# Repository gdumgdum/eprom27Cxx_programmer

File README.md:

# Programmer for EPROM 27 series (27C16-801/2KB-1MB) based on Arduino Micro

Programming is made possible by a dedicated hardware (made of a PCB, a few very common SMD components and an Arduino Micro), and a Qt software that can be compiled for Windows, Linux and MacOS.

Compatible Eprom List (not all chips were tested):

 * 27C16 (2KB)
 * 27C32 (4KB)
 * 27C64 (8KB)
 * 27C128 (16KB)
 * 27C256 (32KB)
 * 27C512 (64KB)
 * 27C1001 (128KB)
 * 27C2001 (256KB)
 * 27C4001 (512KB)
 * 27C801 (1MB)

Selected chip needs to be inserted in the ZIF socket at the lowest position possible (bottom aligned).

Before writing, activate the Voltage functionality, then adjust the potentiometer and compare the measured value with the one specified in the datasheet of the selected eprom. 

# Schematic

Based on the project https://github.com/walhi/arduino_eprom27_programmer, which was based on https://github.com/bouletmarc/BMBurner

PCB is now generated with [Kicad](https://www.kicad.org)

Gerber files generated by Kicad are located [here](https://github.com/gdumgdum/eprom27Cxx_programmer/blob/master/Kicad/Gerber/)

# Software

Software for Windows/Mac/Linux is written with Qt5.

Functions:

 * Read chip to memory buffer and check if chip is blank
 * Save memory buffer to file
 * Read memory buffer from file
 * Program chip with memory buffer
 * Read chip and compare to memory buffer 
 * Programming voltage control

# History

## PCB

* Switched to Arduino Micro model because the Nano version used in the previous version doesn't have enough inputs/outputs to handle all the programming modes.
* Pull-down resistors added to the lines where signal/power is sent through diodes.
* Programming voltage is now only generated from the +5V provided by the Arduino.
* A connector is available to connect to an external power-supply if the USB is not able to provide enough current (should not be necessary if connected to a USB-3 socket).

## Arduino Micro

* Added a reset routine because Micro is not reset when the COM port is opened, contrary to Nano.
* Added a decent synchronisation between Qt application and Arduino when programming the Eprom.
* Added a delay before reading/writting to allow voltages to stabilize.
* Added support for 27C1001, 27C2001, 27C4001 and 27C801.
* Increased communication speed with Qt application to 115200 bauds.

## Qt application

* Detached the buffer display in an independant window.
* Allow main window resizing.
* Fixed the progress bar display on MacOS.
* Added support for 27C1001, 27C2001, 27C4001 and 27C801.
* Added a decent synchronisation between Qt application and Arduino when programming the Eprom.
* Increased communication speed with Arduino to 115200 bauds.

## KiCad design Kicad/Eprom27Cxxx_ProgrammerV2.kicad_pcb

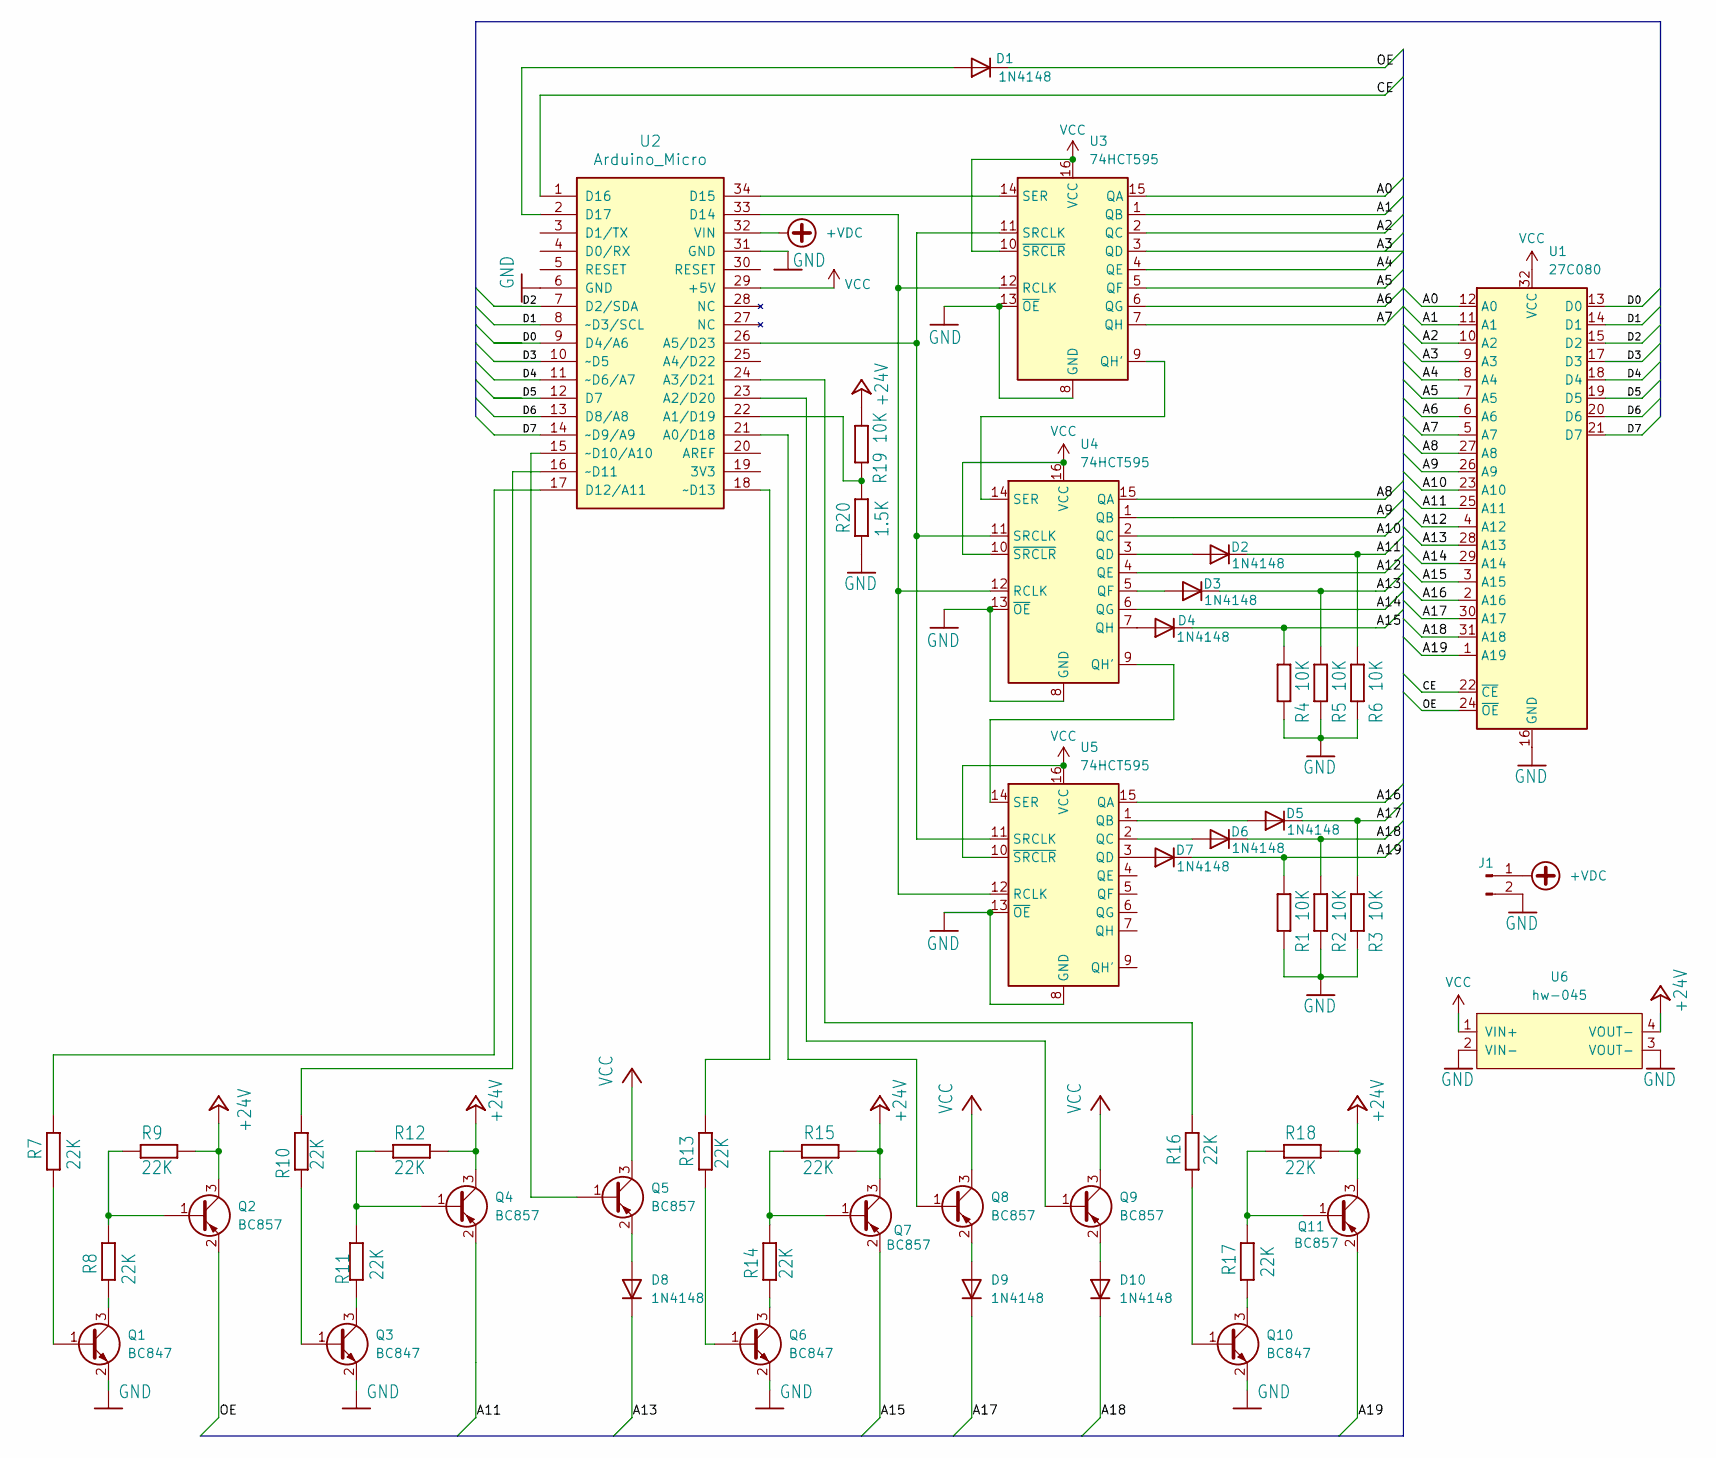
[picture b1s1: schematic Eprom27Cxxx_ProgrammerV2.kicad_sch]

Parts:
D1, D2, D3, D4, D5, D6, D7, D8, D9, D10: 1N4148; D_1206_3216Metric
J1: Conn_01x02_Pin; PinHeader_1x02_P2.54mm_Vertical
Q1, Q3, Q6, Q10: BC847; SOT-23
Q2, Q4, Q5, Q7, Q8, Q9, Q11: BC857; SOT-23
R1, R2, R3, R4, R5, R6, R19: 10K; M0805
R7, R8, R9, R10, R11, R12, R13, R14, R15, R16, R17, R18: 22K; M0805
R20: 1.5K; M0805
U1: 27C080; DIP_Socket-32_W11.9_W12.7_W15.24_W17.78_W18.5_3M_232-1285-0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
U2: Arduino_Micro
U3, U4, U5: 74HCT595; SO16
U6: hw-045

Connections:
+24V: Q2.3 (C), Q4.3 (C), Q7.3 (C), Q11.3 (C), R9.2, R12.2, R15.2, R18.2, R19.1, U6.4 (VOUT-)
+VDC: J1.1, U2.32 (VIN)
/A0: U1.12 (A0), U3.15 (QA)
/A1: U1.11 (A1), U3.1 (QB)
/A2: U1.10 (A2), U3.2 (QC)
/A3: U1.9 (A3), U3.3 (QD)
/A4: U1.8 (A4), U3.4 (QE)
/A5: U1.7 (A5), U3.5 (QF)
/A6: U1.6 (A6), U3.6 (QG)
/A7: U1.5 (A7), U3.7 (QH)
/A8: U1.27 (A8), U4.15 (QA)
/A9: U1.26 (A9), U4.1 (QB)
/A10: U1.23 (A10), U4.2 (QC)
/A11: D2.1 (K), Q4.2 (E), R6.1, U1.25 (A11)
/A12: U1.4 (A12), U4.4 (QE)
/A13: D3.1 (K), D8.1 (K), R5.1, U1.28 (A13)
/A14: U1.29 (A14), U4.6 (QG)
/A15: D4.1 (K), Q7.2 (E), R4.1, U1.3 (A15)
/A16: U1.2 (A16), U5.15 (QA)
/A17: D5.1 (K), D9.1 (K), R3.1, U1.30 (A17)
/A18: D6.1 (K), D10.1 (K), R2.1, U1.31 (A18)
/A19: D7.1 (K), Q11.2 (E), R1.1, U1.1 (A19)
/CE: U1.22 (~CE), U2.1 (D16)
/D0: U1.13 (D0), U2.9 (D4/A6)
/D1: U1.14 (D1), U2.8 (~D3/SCL)
/D2: U1.15 (D2), U2.7 (D2/SDA)
/D3: U1.17 (D3), U2.10 (~D5)
/D4: U1.18 (D4), U2.11 (~D6/A7)
/D5: U1.19 (D5), U2.12 (D7)
/D6: U1.20 (D6), U2.13 (D8/A8)
/D7: U1.21 (D7), U2.14 (~D9/A9)
/OE: D1.1 (K), Q2.2 (E), U1.24 (~OE)
GND: J1.2, Q1.2 (E), Q3.2 (E), Q6.2 (E), Q10.2 (E), R1.2, R2.2, R3.2, R4.2, R5.2, R6.2, R20.2, U1.16 (GND), U2.6 (GND), U2.31 (GND), U3.8 (GND), U3.13 (~OE), U4.8 (GND), U4.13 (~OE), U5.8 (GND), U5.13 (~OE), U6.2 (VIN-), U6.3 (VOUT-)
unnamed: D1.2 (A), U2.2 (D17)
unnamed: D2.2 (A), U4.3 (QD)
unnamed: D3.2 (A), U4.5 (QF)
unnamed: D4.2 (A), U4.7 (QH)
unnamed: D5.2 (A), U5.1 (QB)
unnamed: D6.2 (A), U5.2 (QC)
unnamed: D7.2 (A), U5.3 (QD)
unnamed: D8.2 (A), Q5.2 (E)
unnamed: D9.2 (A), Q8.2 (E)
unnamed: D10.2 (A), Q9.2 (E)
unnamed: Q1.1 (B), R7.2
unnamed: Q1.3 (C), R8.2
unnamed: Q2.1 (B), R8.1, R9.1
unnamed: Q3.1 (B), R10.2
unnamed: Q3.3 (C), R11.2
unnamed: Q4.1 (B), R11.1, R12.1
unnamed: Q5.1 (B), U2.15 (~D10/A10)
unnamed: Q6.1 (B), R13.1
unnamed: Q6.3 (C), R14.1
unnamed: Q7.1 (B), R14.2, R15.1
unnamed: Q8.1 (B), U2.21 (A0/D18)
unnamed: Q9.1 (B), U2.23 (A2/D20)
unnamed: Q10.1 (B), R16.2
unnamed: Q10.3 (C), R17.2
unnamed: Q11.1 (B), R17.1, R18.1
unnamed: R19.2, R20.1, U2.22 (A1/D19)
unnamed: R16.1, U2.24 (A3/D21)
unnamed: U2.26 (A5/D23), U3.11 (SRCLK), U4.11 (SRCLK), U5.11 (SRCLK)
unnamed: R7.1, U2.17 (D12/A11)
unnamed: U2.33 (D14), U3.12 (RCLK), U4.12 (RCLK), U5.12 (RCLK)
unnamed: U2.34 (D15), U3.14 (SER)
unnamed: R10.1, U2.16 (~D11)
unnamed: R13.2, U2.18 (~D13)
unnamed: U3.9 (QH'), U4.14 (SER)
unnamed: U4.9 (QH'), U5.14 (SER)
VCC: Q5.3 (C), Q8.3 (C), Q9.3 (C), U1.32 (VCC), U2.29 (+5V), U3.10 (~SRCLR), U3.16 (VCC), U4.10 (~SRCLR), U4.16 (VCC), U5.10 (~SRCLR), U5.16 (VCC), U6.1 (VIN+)

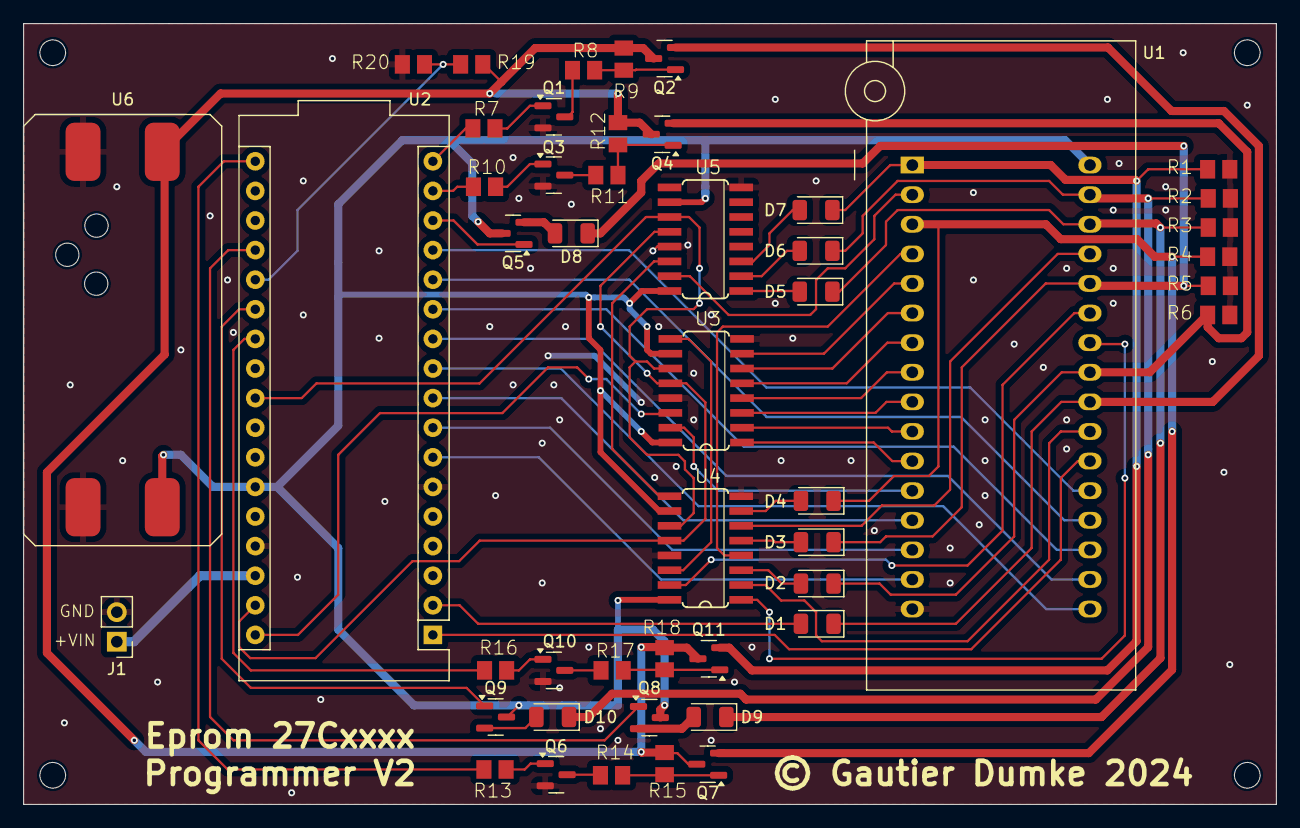
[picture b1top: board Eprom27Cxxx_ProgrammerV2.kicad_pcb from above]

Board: 2 copper layers, 107.5 x 67.0 mm, 48 parts (0 on the bottom side), 69 nets.

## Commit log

2024-05-11 V2 with more supported eproms

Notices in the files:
Kicad/Eprom27Cxxx_ProgrammerV2.kicad_pcb:
© Gautier Dumke 2024
